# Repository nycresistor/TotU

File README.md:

TotU
====

Temple of the Unticketed

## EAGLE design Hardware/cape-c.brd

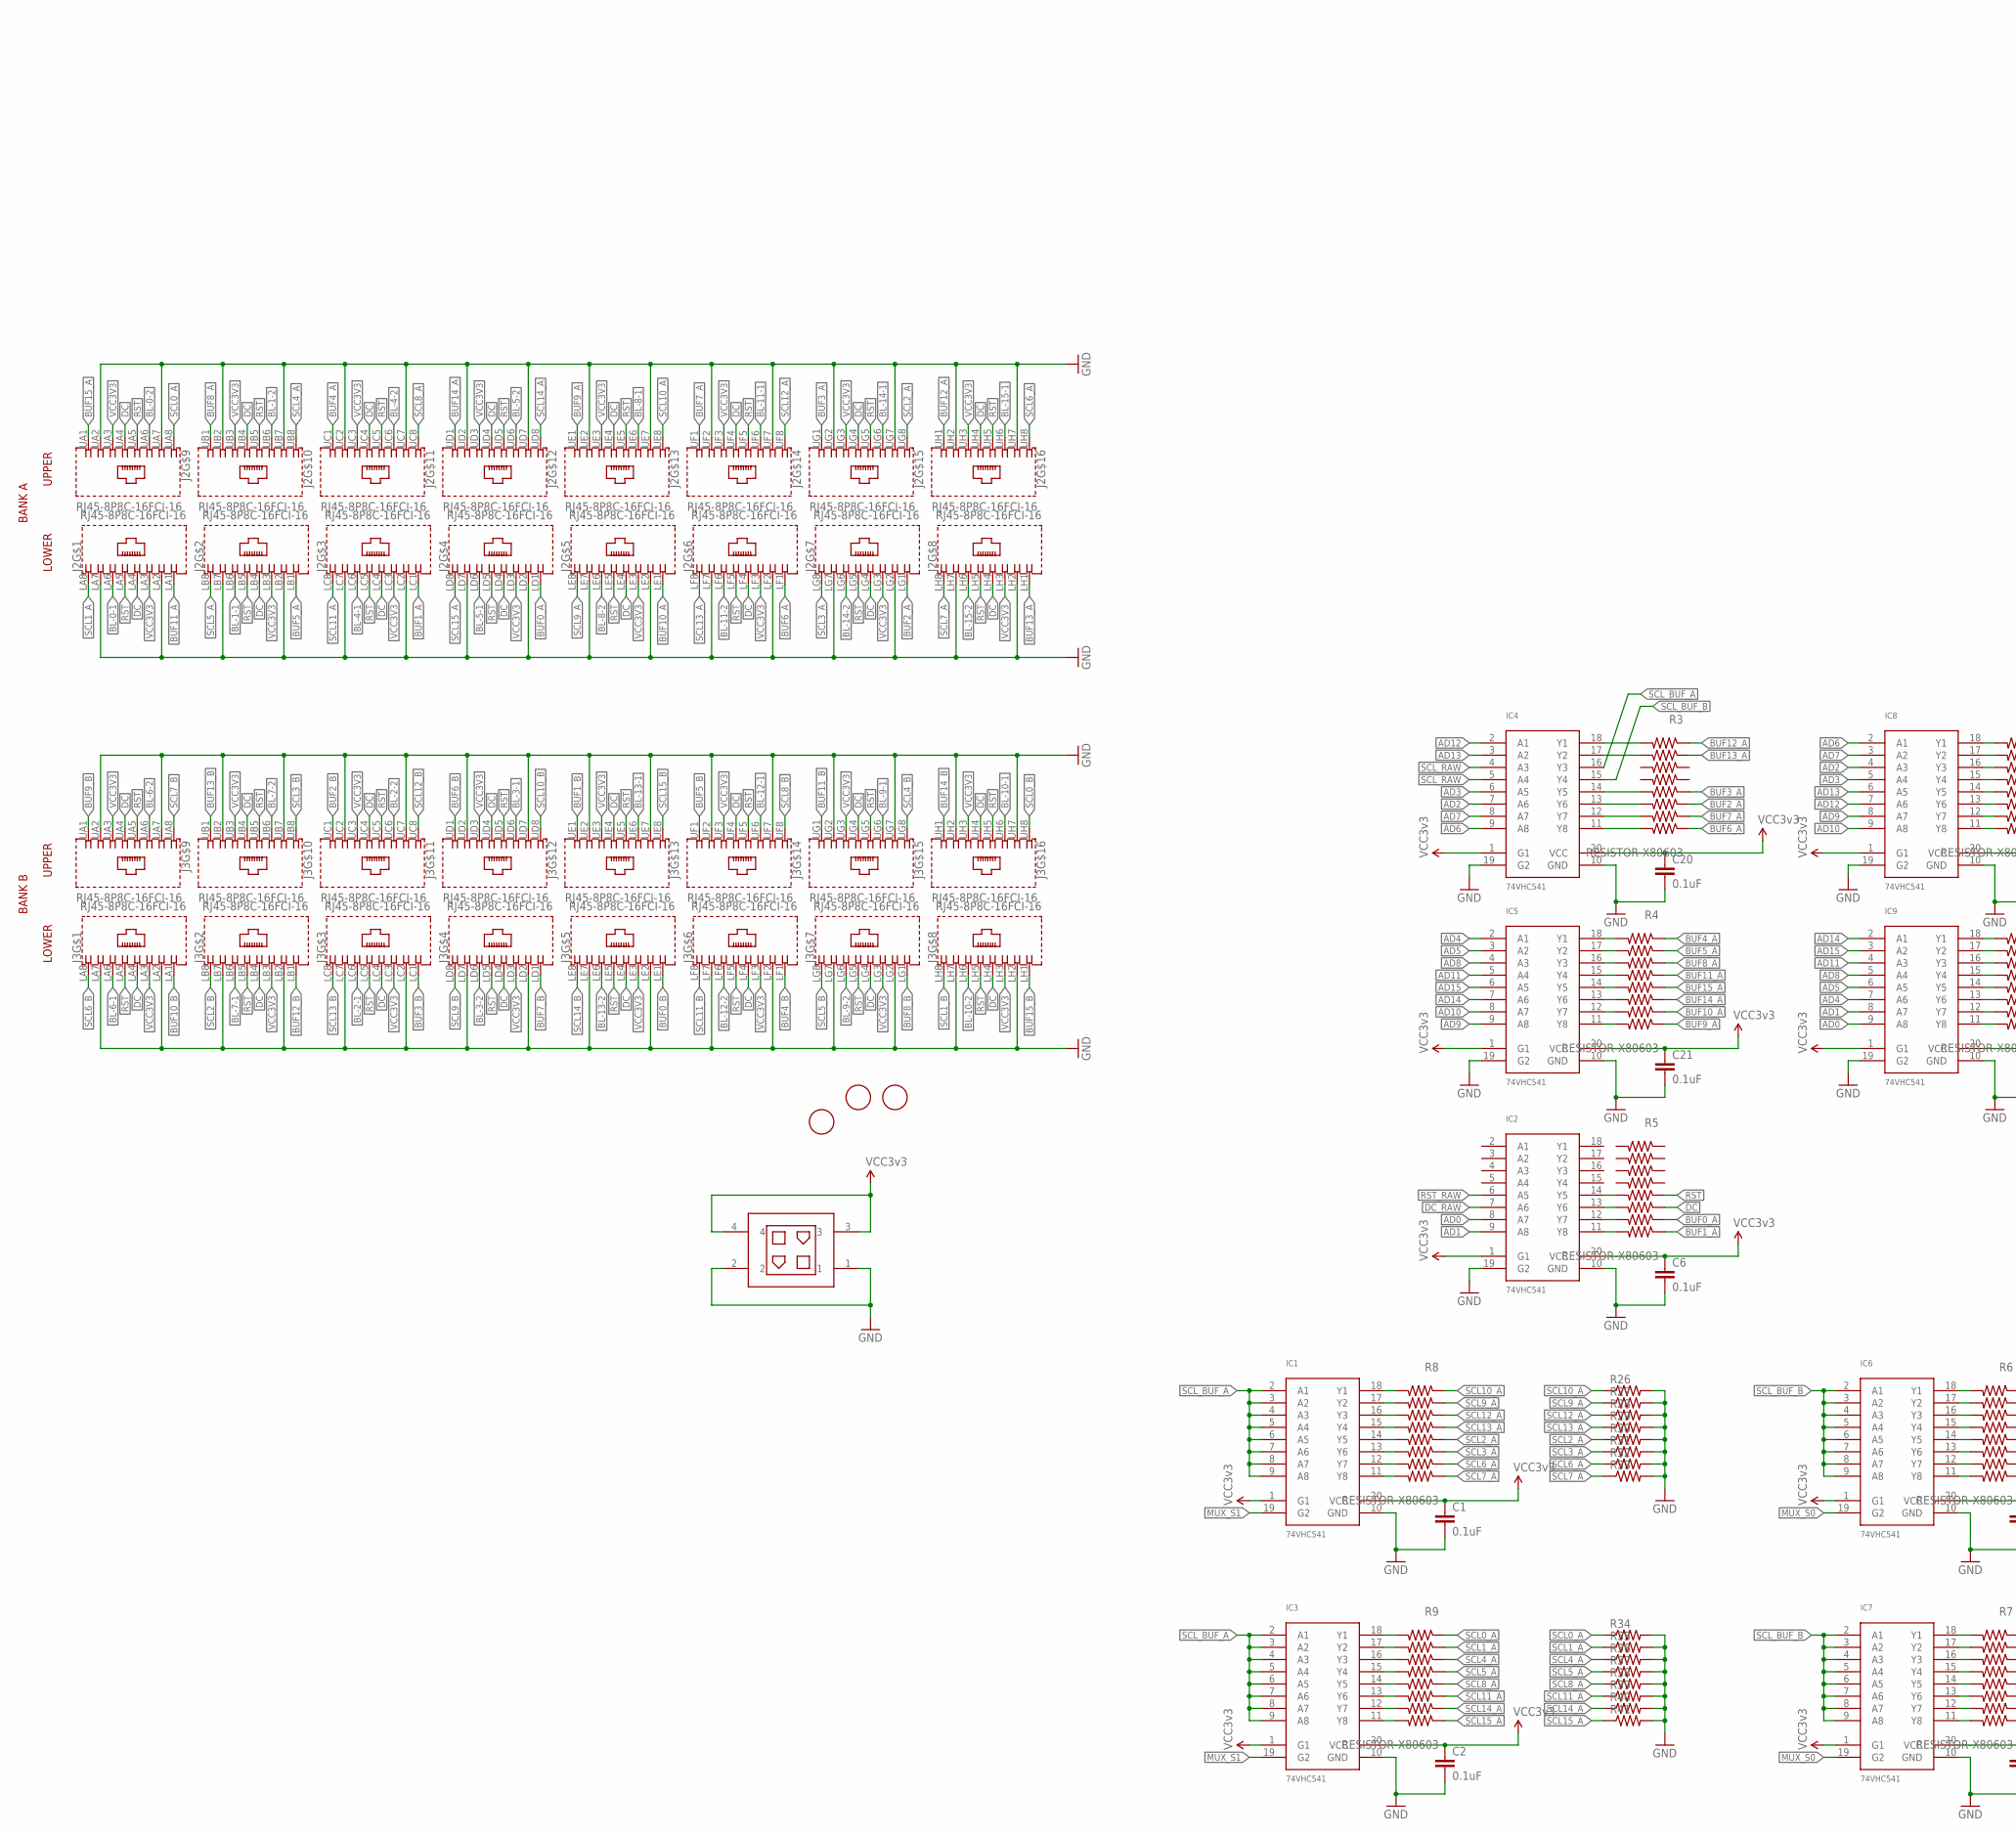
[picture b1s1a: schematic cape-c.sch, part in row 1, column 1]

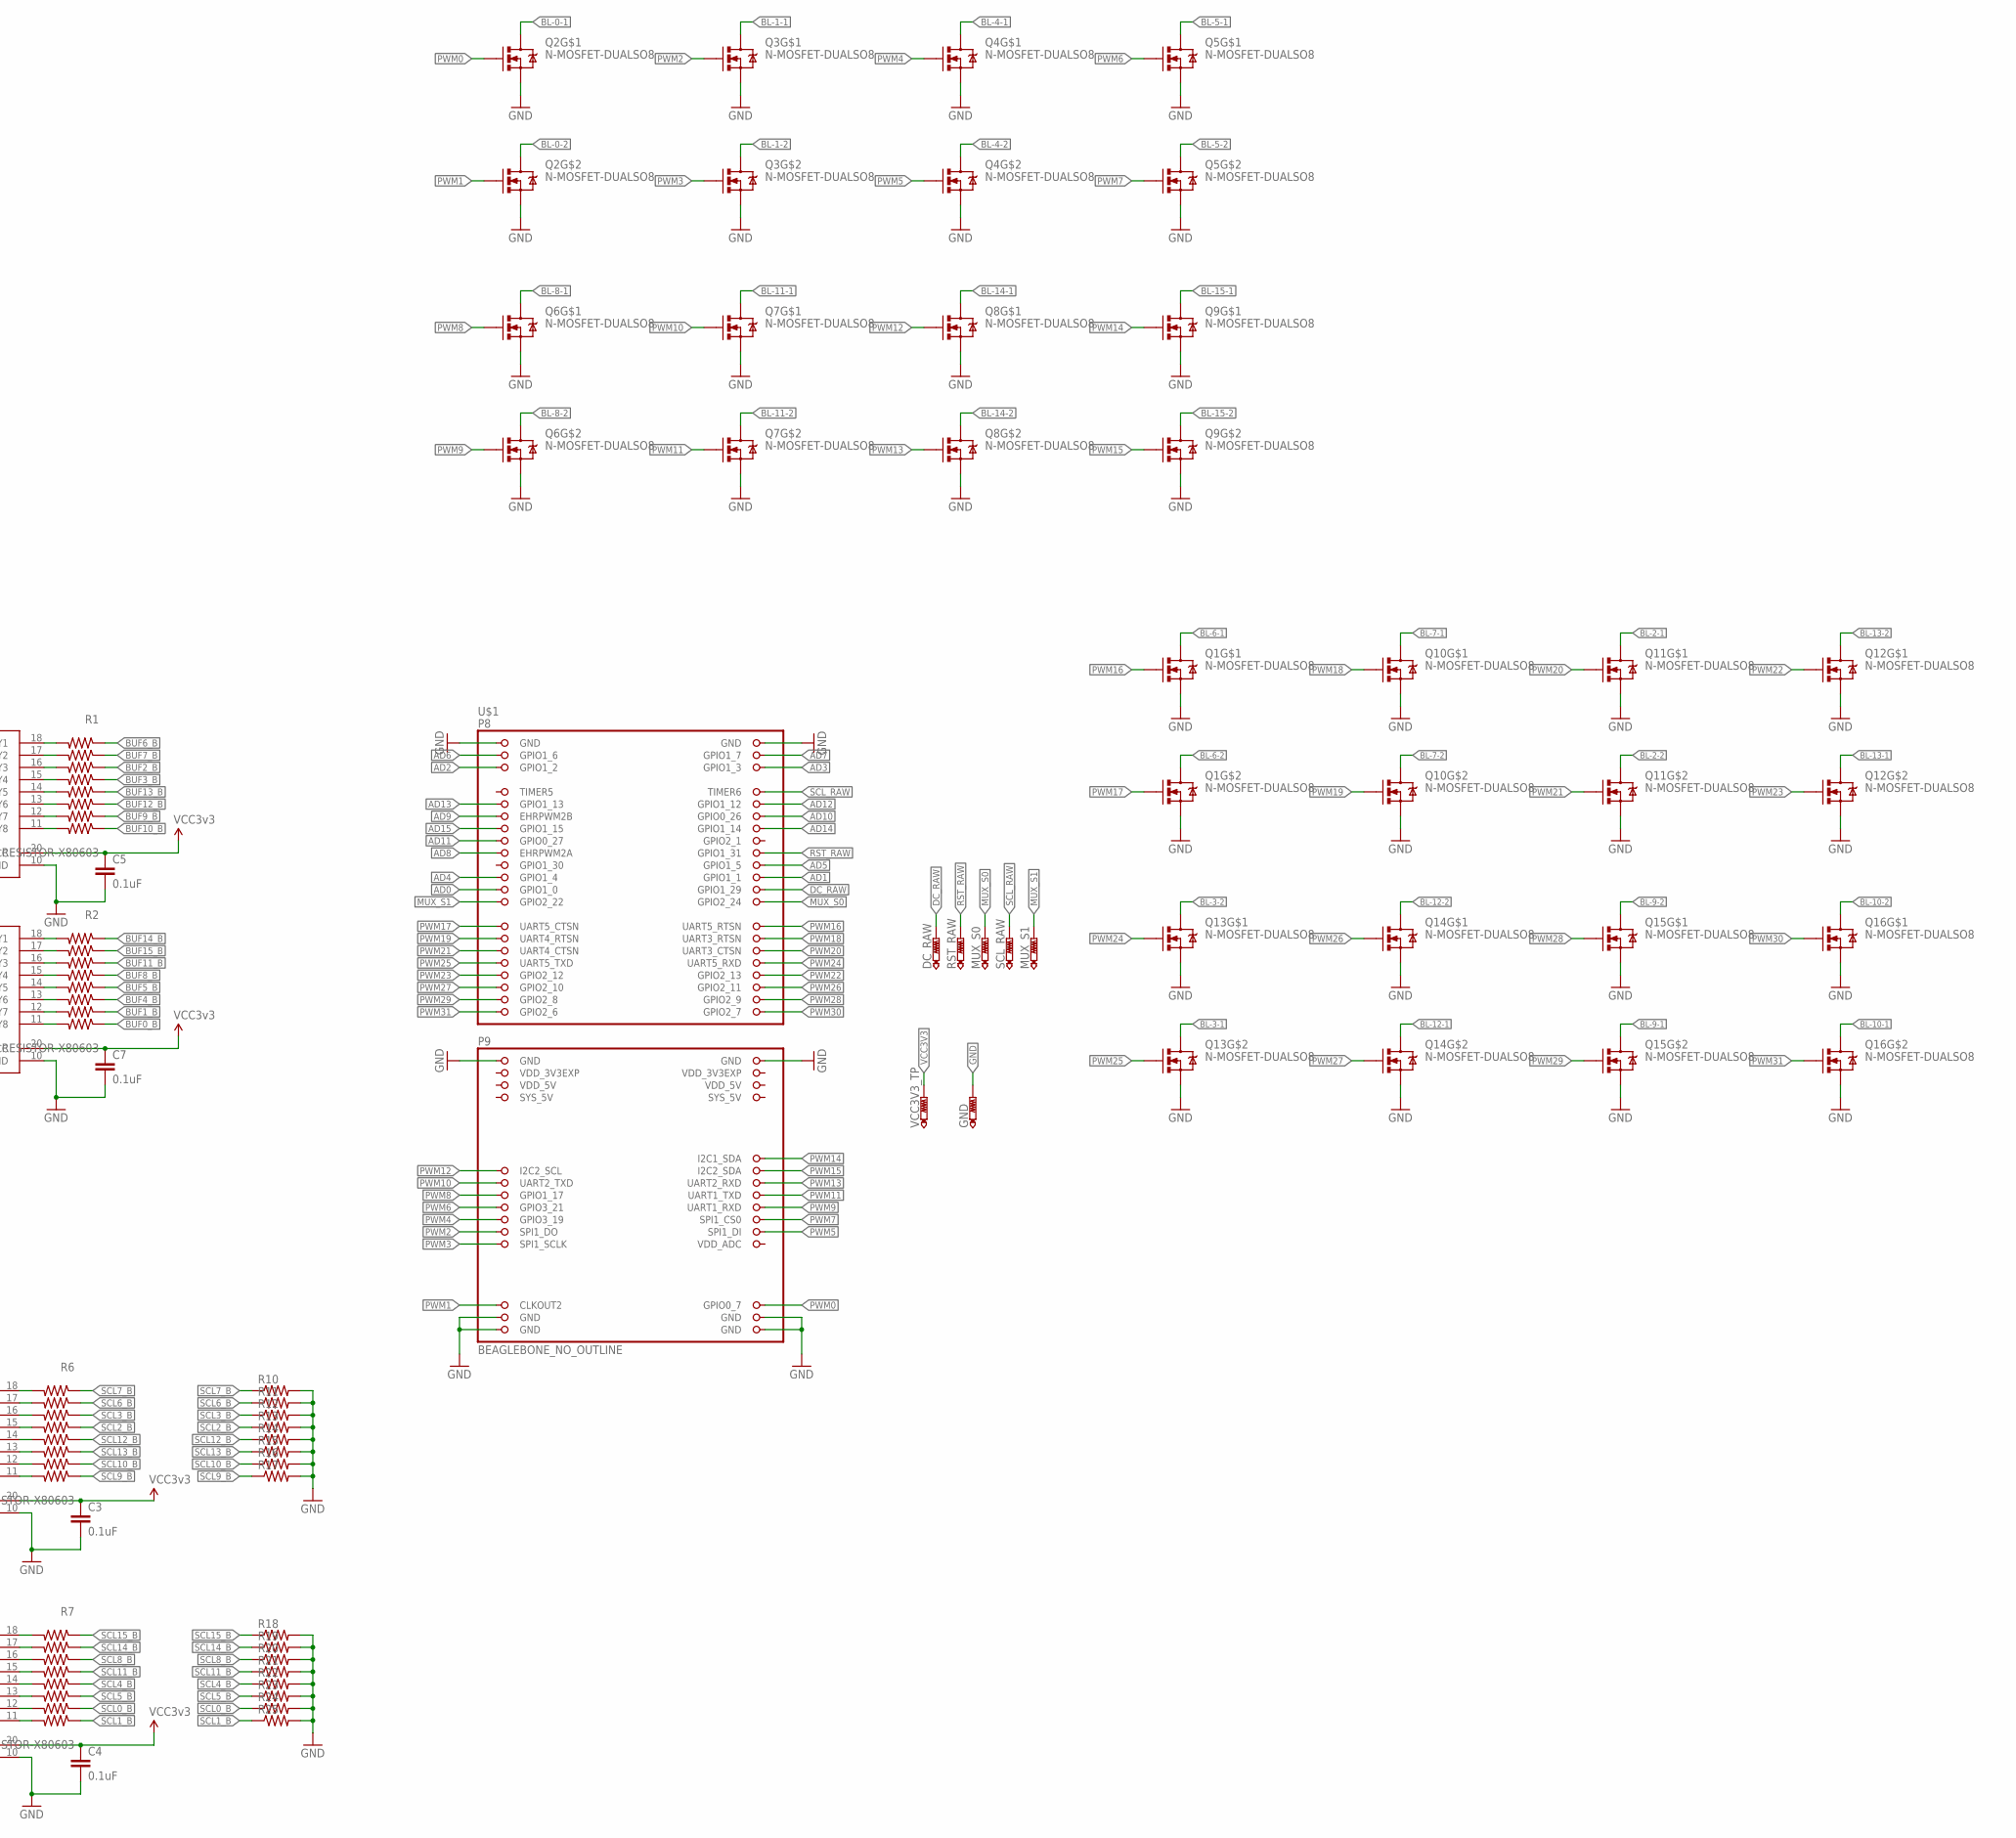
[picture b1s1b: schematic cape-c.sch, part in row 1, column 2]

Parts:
C1, C2, C3, C4, C5, C6, C7, C20, C21: 0.1uF; 0805
DC_RAW: PTR1TP10R; TP10R
GND: PTR1TP15SQ; TP15SQ
IC1, IC2, IC3, IC4, IC5, IC6, IC7, IC8, IC9: 74VHC541; TSSOP20; PARTNO MC74LCX245DTR2G
J1: MOLEX-P4
J2, J3: RJ45-8P8C-16FCI-16; FCI-10118074-500A010LF; PARTNO 10118074-500A010LF
MUX_S0, MUX_S1: PTR1TP10R; TP10R
Q1, Q2, Q3, Q4, Q5, Q6, Q7, Q8, Q9, Q10, Q11, Q12, Q13, Q14, Q15, Q16: N-MOSFET-DUALSO8; SO8; PARTNO DMN6040SSD-13
R1, R2, R3, R4, R5, R6, R7, R8, R9: RESISTOR-X80603; R0603-X8; PARTNO 742C163220JP
R10, R11, R12, R13, R14, R15, R16, R17, R18, R19, R20, R21, R22, R23, R24, R25, R26, R27, R28, R29, R30, R31, R32, R33, R34, R35, R36, R37, R38, R39, R40, R41: RESISTOR0603-RES; 0603-RES
RST_RAW: PTR1TP10R; TP10R
SCL_RAW: PTR1TP10R; TP10R
U$1: BEAGLEBONE_NO_OUTLINE; BEAGLEBONE_SHIELD_NO_OUTLINE
U$4, U$5, U$6: FIDUCIAL; FIDUCIAL_1MM
VCC3V3_TP: PTR1TP15R; TP15R

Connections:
AD0: IC2.8 (A7), IC9.9 (A8), U$1.25 (GPIO1_0)
AD1: IC2.9 (A8), IC9.8 (A7), U$1.24 (GPIO1_1)
AD2: IC4.7 (A6), IC8.4 (A3), U$1.5 (GPIO1_2)
AD3: IC4.6 (A5), IC8.5 (A4), U$1.6 (GPIO1_3)
AD4: IC5.2 (A1), IC9.7 (A6), U$1.23 (GPIO1_4)
AD5: IC5.3 (A2), IC9.6 (A5), U$1.22 (GPIO1_5)
AD6: IC4.9 (A8), IC8.2 (A1), U$1.3 (GPIO1_6)
AD7: IC4.8 (A7), IC8.3 (A2), U$1.4 (GPIO1_7)
AD8: IC5.4 (A3), IC9.5 (A4), U$1.19 (EHRPWM2A)
AD9: IC5.9 (A8), IC8.8 (A7), U$1.13 (EHRPWM2B)
AD10: IC5.8 (A7), IC8.9 (A8), U$1.14 (GPIO0_26)
AD11: IC5.5 (A4), IC9.4 (A3), U$1.17 (GPIO0_27)
AD12: IC4.2 (A1), IC8.7 (A6), U$1.12 (GPIO1_12)
AD13: IC4.3 (A2), IC8.6 (A5), U$1.11 (GPIO1_13)
AD14: IC5.7 (A6), IC9.2 (A1), U$1.16 (GPIO1_14)
AD15: IC5.6 (A5), IC9.3 (A2), U$1.15 (GPIO1_15)
BL-0-1: J2.LA6 (6), Q2.7 (D), Q2.8 (D)
BL-0-2: J2.UA6 (6), Q2.5 (D), Q2.6 (D)
BL-1-1: J2.LB6 (6), Q3.7 (D), Q3.8 (D)
BL-1-2: J2.UB6 (6), Q3.5 (D), Q3.6 (D)
BL-2-1: J3.LC6 (6), Q11.7 (D), Q11.8 (D)
BL-2-2: J3.UC6 (6), Q11.5 (D), Q11.6 (D)
BL-3-1: J3.UD6 (6), Q13.5 (D), Q13.6 (D)
BL-3-2: J3.LD6 (6), Q13.7 (D), Q13.8 (D)
BL-4-1: J2.LC6 (6), Q4.7 (D), Q4.8 (D)
BL-4-2: J2.UC6 (6), Q4.5 (D), Q4.6 (D)
BL-5-1: J2.LD6 (6), Q5.7 (D), Q5.8 (D)
BL-5-2: J2.UD6 (6), Q5.5 (D), Q5.6 (D)
BL-6-1: J3.LA6 (6), Q1.7 (D), Q1.8 (D)
BL-6-2: J3.UA6 (6), Q1.5 (D), Q1.6 (D)
BL-7-1: J3.LB6 (6), Q10.7 (D), Q10.8 (D)
BL-7-2: J3.UB6 (6), Q10.5 (D), Q10.6 (D)
BL-8-1: J2.UE6 (6), Q6.7 (D), Q6.8 (D)
BL-8-2: J2.LE6 (6), Q6.5 (D), Q6.6 (D)
BL-9-1: J3.UG6 (6), Q15.5 (D), Q15.6 (D)
BL-9-2: J3.LG6 (6), Q15.7 (D), Q15.8 (D)
BL-10-1: J3.UH6 (6), Q16.5 (D), Q16.6 (D)
BL-10-2: J3.LH6 (6), Q16.7 (D), Q16.8 (D)
BL-11-1: J2.UF6 (6), Q7.7 (D), Q7.8 (D)
BL-11-2: J2.LF6 (6), Q7.5 (D), Q7.6 (D)
BL-12-1: J3.UF6 (6), Q14.5 (D), Q14.6 (D)
BL-12-2: J3.LF6 (6), Q14.7 (D), Q14.8 (D)
BL-13-1: J3.UE6 (6), Q12.5 (D), Q12.6 (D)
BL-13-2: J3.LE6 (6), Q12.7 (D), Q12.8 (D)
BL-14-1: J2.UG6 (6), Q8.7 (D), Q8.8 (D)
BL-14-2: J2.LG6 (6), Q8.5 (D), Q8.6 (D)
BL-15-1: J2.UH6 (6), Q9.7 (D), Q9.8 (D)
BL-15-2: J2.LH6 (6), Q9.5 (D), Q9.6 (D)
BUF0_A: J2.LD1 (1), R5.7A (7B)
BUF0_B: J3.LE1 (1), R2.8A (8B)
BUF1_A: J2.LC1 (1), R5.8A (8B)
BUF1_B: J3.UE1 (1), R2.7A (7B)
BUF2_A: J2.LG1 (1), R3.6A (6B)
BUF2_B: J3.UC1 (1), R1.3A (3B)
BUF3_A: J2.UG1 (1), R3.5A (5B)
BUF3_B: J3.LC1 (1), R1.4A (4B)
BUF4_A: J2.UC1 (1), R4.1A (1B)
BUF4_B: J3.LF1 (1), R2.6A (6B)
BUF5_A: J2.LB1 (1), R4.2A (2B)
BUF5_B: J3.UF1 (1), R2.5A (5B)
BUF6_A: J2.LF1 (1), R3.8A (8B)
BUF6_B: J3.UD1 (1), R1.1A (1B)
BUF7_A: J2.UF1 (1), R3.7A (7B)
BUF7_B: J3.LD1 (1), R1.2A (2B)
BUF8_A: J2.UB1 (1), R4.3A (3B)
BUF8_B: J3.LG1 (1), R2.4A (4B)
BUF9_A: J2.UE1 (1), R4.8A (8B)
BUF9_B: J3.UA1 (1), R1.7A (7B)
BUF10_A: J2.LE1 (1), R4.7A (7B)
BUF10_B: J3.LA1 (1), R1.8A (8B)
BUF11_A: J2.LA1 (1), R4.4A (4B)
BUF11_B: J3.UG1 (1), R2.3A (3B)
BUF12_A: J2.UH1 (1), R3.1A (1B)
BUF12_B: J3.LB1 (1), R1.6A (6B)
BUF13_A: J2.LH1 (1), R3.2A (2B)
BUF13_B: J3.UB1 (1), R1.5A (5B)
BUF14_A: J2.UD1 (1), R4.6A (6B)
BUF14_B: J3.UH1 (1), R2.1A (1B)
BUF15_A: J2.UA1 (1), R4.5A (5B)
BUF15_B: J3.LH1 (1), R2.2A (2B)
DC: J2.LA4 (4), J2.LB4 (4), J2.LC4 (4), J2.LD4 (4), J2.LE4 (4), J2.LF4 (4), J2.LG4 (4), J2.LH4 (4), J2.UA4 (4), J2.UB4 (4), J2.UC4 (4), J2.UD4 (4), J2.UE4 (4), J2.UF4 (4), J2.UG4 (4), J2.UH4 (4), J3.LA4 (4), J3.LB4 (4), J3.LC4 (4), J3.LD4 (4), J3.LE4 (4), J3.LF4 (4), J3.LG4 (4), J3.LH4 (4), J3.UA4 (4), J3.UB4 (4), J3.UC4 (4), J3.UD4 (4), J3.UE4 (4), J3.UF4 (4), J3.UG4 (4), J3.UH4 (4), R5.6A (6B)
DC_RAW: DC_RAW.TP, IC2.7 (A6), U$1.26 (GPIO1_29)
GND: C1.2, C2.2, C3.2, C4.2, C5.2, C6.2, C7.2, C20.2, C21.2, GND.TP, IC1.10 (GND), IC2.10 (GND), IC2.19 (G2), IC3.10 (GND), IC4.10 (GND), IC4.19 (G2), IC5.10 (GND), IC5.19 (G2), IC6.10 (GND), IC7.10 (GND), IC8.10 (GND), IC8.19 (G2), IC9.10 (GND), IC9.19 (G2), J1.1, J1.2, J2.LA2 (2), J2.LA7 (7), J2.LB2 (2), J2.LB7 (7), J2.LC2 (2), J2.LC7 (7), J2.LD2 (2), J2.LD7 (7), J2.LE2 (2), J2.LE7 (7), J2.LF2 (2), J2.LF7 (7), J2.LG2 (2), J2.LG7 (7), J2.LH2 (2), J2.LH7 (7), J2.UA2 (2), J2.UA7 (7), J2.UB2 (2), J2.UB7 (7), J2.UC2 (2), J2.UC7 (7), J2.UD2 (2), J2.UD7 (7), J2.UE2 (2), J2.UE7 (7), J2.UF2 (2), J2.UF7 (7), J2.UG2 (2), J2.UG7 (7), J2.UH2 (2), J2.UH7 (7), J3.LA2 (2), J3.LA7 (7), J3.LB2 (2), J3.LB7 (7), J3.LC2 (2), J3.LC7 (7), J3.LD2 (2), J3.LD7 (7), J3.LE2 (2), J3.LE7 (7), J3.LF2 (2), J3.LF7 (7), J3.LG2 (2), J3.LG7 (7), J3.LH2 (2), J3.LH7 (7), J3.UA2 (2), J3.UA7 (7), J3.UB2 (2), J3.UB7 (7), J3.UC2 (2), J3.UC7 (7), J3.UD2 (2), J3.UD7 (7), J3.UE2 (2), J3.UE7 (7), J3.UF2 (2), J3.UF7 (7), J3.UG2 (2), J3.UG7 (7), J3.UH2 (2), J3.UH7 (7), Q1.1 (S), Q1.3 (S), Q2.1 (S), Q2.3 (S), Q3.1 (S), Q3.3 (S), Q4.1 (S), Q4.3 (S), Q5.1 (S), Q5.3 (S), Q6.1 (S), Q6.3 (S), Q7.1 (S), Q7.3 (S), Q8.1 (S), Q8.3 (S), Q9.1 (S), Q9.3 (S), Q10.1 (S), Q10.3 (S), Q11.1 (S), Q11.3 (S), Q12.1 (S), Q12.3 (S), Q13.1 (S), Q13.3 (S), Q14.1 (S), Q14.3 (S), Q15.1 (S), Q15.3 (S), Q16.1 (S), Q16.3 (S), R10.2, R11.2, R12.2, R13.2, R14.2, R15.2, R16.2, R17.2, R18.2, R19.2, R20.2, R21.2, R22.2, R23.2, R24.2, R25.2, R26.2, R27.2, R28.2, R29.2, R30.2, R31.2, R32.2, R33.2, R34.2, R35.2, R36.2, R37.2, R38.2, R39.2, R40.2, R41.2, U$1.1 (GND), U$1.2 (GND), U$1.47 (GND), U$1.48 (GND), U$1.89 (GND), U$1.90 (GND), U$1.91 (GND), U$1.92 (GND)
MUX_S0: IC6.19 (G2), IC7.19 (G2), MUX_S0.TP, U$1.28 (GPIO2_24)
MUX_S1: IC1.19 (G2), IC3.19 (G2), MUX_S1.TP, U$1.27 (GPIO2_22)
unnamed: IC2.14 (Y5), R5.5B (5A)
unnamed: IC2.13 (Y6), R5.6B (6A)
unnamed: IC8.18 (Y1), R1.1B (1A)
unnamed: IC8.17 (Y2), R1.2B (2A)
unnamed: IC8.16 (Y3), R1.3B (3A)
unnamed: IC8.15 (Y4), R1.4B (4A)
unnamed: IC8.14 (Y5), R1.5B (5A)
unnamed: IC8.13 (Y6), R1.6B (6A)
unnamed: IC8.12 (Y7), R1.7B (7A)
unnamed: IC8.11 (Y8), R1.8B (8A)
unnamed: IC9.18 (Y1), R2.1B (1A)
unnamed: IC9.17 (Y2), R2.2B (2A)
unnamed: IC9.16 (Y3), R2.3B (3A)
unnamed: IC9.15 (Y4), R2.4B (4A)
unnamed: IC9.14 (Y5), R2.5B (5A)
unnamed: IC9.13 (Y6), R2.6B (6A)
unnamed: IC9.12 (Y7), R2.7B (7A)
unnamed: IC9.11 (Y8), R2.8B (8A)
unnamed: IC5.18 (Y1), R4.1B (1A)
unnamed: IC5.17 (Y2), R4.2B (2A)
unnamed: IC5.16 (Y3), R4.3B (3A)
unnamed: IC5.15 (Y4), R4.4B (4A)
unnamed: IC5.13 (Y6), R4.6B (6A)
unnamed: IC5.14 (Y5), R4.5B (5A)
unnamed: IC5.12 (Y7), R4.7B (7A)
unnamed: IC5.11 (Y8), R4.8B (8A)
unnamed: IC4.18 (Y1), R3.1B (1A)
unnamed: IC4.17 (Y2), R3.2B (2A)
unnamed: IC6.18 (Y1), R6.1B (1A)
unnamed: IC2.12 (Y7), R5.7B (7A)
unnamed: IC4.14 (Y5), R3.5B (5A)
unnamed: IC4.13 (Y6), R3.6B (6A)
unnamed: IC4.12 (Y7), R3.7B (7A)
unnamed: IC4.11 (Y8), R3.8B (8A)
unnamed: IC2.11 (Y8), R5.8B (8A)
unnamed: IC6.17 (Y2), R6.2B (2A)
unnamed: IC6.16 (Y3), R6.3B (3A)
unnamed: IC6.15 (Y4), R6.4B (4A)
unnamed: IC6.14 (Y5), R6.5B (5A)
unnamed: IC6.13 (Y6), R6.6B (6A)
unnamed: IC6.12 (Y7), R6.7B (7A)
unnamed: IC6.11 (Y8), R6.8B (8A)
unnamed: IC7.18 (Y1), R7.1B (1A)
unnamed: IC7.17 (Y2), R7.2B (2A)
unnamed: IC7.15 (Y4), R7.4B (4A)
unnamed: IC7.16 (Y3), R7.3B (3A)
unnamed: IC7.14 (Y5), R7.5B (5A)
unnamed: IC7.12 (Y7), R7.7B (7A)
unnamed: IC7.13 (Y6), R7.6B (6A)
unnamed: IC7.11 (Y8), R7.8B (8A)
unnamed: IC1.18 (Y1), R8.1B (1A)
unnamed: IC1.17 (Y2), R8.2B (2A)
unnamed: IC1.16 (Y3), R8.3B (3A)
unnamed: IC1.15 (Y4), R8.4B (4A)
unnamed: IC1.14 (Y5), R8.5B (5A)
unnamed: IC1.13 (Y6), R8.6B (6A)
unnamed: IC1.12 (Y7), R8.7B (7A)
unnamed: IC1.11 (Y8), R8.8B (8A)
unnamed: IC3.18 (Y1), R9.1B (1A)
unnamed: IC3.17 (Y2), R9.2B (2A)
unnamed: IC3.16 (Y3), R9.3B (3A)
unnamed: IC3.15 (Y4), R9.4B (4A)
unnamed: IC3.14 (Y5), R9.5B (5A)
unnamed: IC3.13 (Y6), R9.6B (6A)
unnamed: IC3.12 (Y7), R9.7B (7A)
unnamed: IC3.11 (Y8), R9.8B (8A)
PWM0: Q2.2 (G), U$1.88 (GPIO0_7)
PWM1: Q2.4 (G), U$1.87 (CLKOUT2)
PWM2: Q3.2 (G), U$1.75 (SPI1_DO)
PWM3: Q3.4 (G), U$1.77 (SPI1_SCLK)
PWM4: Q4.2 (G), U$1.73 (GPIO3_19)
PWM5: Q4.4 (G), U$1.76 (SPI1_DI)
PWM6: Q5.2 (G), U$1.71 (GPIO3_21)
PWM7: Q5.4 (G), U$1.74 (SPI1_CS0)
PWM8: Q6.2 (G), U$1.69 (GPIO1_17)
PWM9: Q6.4 (G), U$1.72 (UART1_RXD)
PWM10: Q7.2 (G), U$1.67 (UART2_TXD)
PWM11: Q7.4 (G), U$1.70 (UART1_TXD)
PWM12: Q8.2 (G), U$1.65 (I2C2_SCL)
PWM13: Q8.4 (G), U$1.68 (UART2_RXD)
PWM14: Q9.2 (G), U$1.64 (I2C1_SDA)
PWM15: Q9.4 (G), U$1.66 (I2C2_SDA)
PWM16: Q1.2 (G), U$1.32 (UART5_RTSN)
PWM17: Q1.4 (G), U$1.31 (UART5_CTSN)
PWM18: Q10.2 (G), U$1.34 (UART3_RTSN)
PWM19: Q10.4 (G), U$1.33 (UART4_RTSN)
PWM20: Q11.2 (G), U$1.36 (UART3_CTSN)
PWM21: Q11.4 (G), U$1.35 (UART4_CTSN)
PWM22: Q12.2 (G), U$1.40 (GPIO2_13)
PWM23: Q12.4 (G), U$1.39 (GPIO2_12)
PWM24: Q13.2 (G), U$1.38 (UART5_RXD)
PWM25: Q13.4 (G), U$1.37 (UART5_TXD)
PWM26: Q14.2 (G), U$1.42 (GPIO2_11)
PWM27: Q14.4 (G), U$1.41 (GPIO2_10)
PWM28: Q15.2 (G), U$1.44 (GPIO2_9)
PWM29: Q15.4 (G), U$1.43 (GPIO2_8)
PWM30: Q16.2 (G), U$1.46 (GPIO2_7)
PWM31: Q16.4 (G), U$1.45 (GPIO2_6)
RST: J2.LA5 (5), J2.LB5 (5), J2.LC5 (5), J2.LD5 (5), J2.LE5 (5), J2.LF5 (5), J2.LG5 (5), J2.LH5 (5), J2.UA5 (5), J2.UB5 (5), J2.UC5 (5), J2.UD5 (5), J2.UE5 (5), J2.UF5 (5), J2.UG5 (5), J2.UH5 (5), J3.LA5 (5), J3.LB5 (5), J3.LC5 (5), J3.LD5 (5), J3.LE5 (5), J3.LF5 (5), J3.LG5 (5), J3.LH5 (5), J3.UA5 (5), J3.UB5 (5), J3.UC5 (5), J3.UD5 (5), J3.UE5 (5), J3.UF5 (5), J3.UG5 (5), J3.UH5 (5), R5.5A (5B)
RST_RAW: IC2.6 (A5), RST_RAW.TP, U$1.20 (GPIO1_31)
SCL0_A: J2.UA8 (8), R9.1A (1B), R34.1
SCL0_B: J3.UH8 (8), R7.7A (7B), R24.1
SCL1_A: J2.LA8 (8), R9.2A (2B), R35.1
SCL1_B: J3.LH8 (8), R7.8A (8B), R25.1
SCL2_A: J2.UG8 (8), R8.5A (5B), R30.1
SCL2_B: J3.LB8 (8), R6.4A (4B), R13.1
SCL3_A: J2.LG8 (8), R8.6A (6B), R31.1
SCL3_B: J3.UB8 (8), R6.3A (3B), R12.1
SCL4_A: J2.UB8 (8), R9.3A (3B), R36.1
SCL4_B: J3.UG8 (8), R7.5A (5B), R22.1
SCL5_A: J2.LB8 (8), R9.4A (4B), R37.1
SCL5_B: J3.LG8 (8), R7.6A (6B), R23.1
SCL6_A: J2.UH8 (8), R8.7A (7B), R32.1
SCL6_B: J3.LA8 (8), R6.2A (2B), R11.1
SCL7_A: J2.LH8 (8), R8.8A (8B), R33.1
SCL7_B: J3.UA8 (8), R6.1A (1B), R10.1
SCL8_A: J2.UC8 (8), R9.5A (5B), R38.1
SCL8_B: J3.UF8 (8), R7.3A (3B), R20.1
SCL9_A: J2.LE8 (8), R8.2A (2B), R27.1
SCL9_B: J3.LD8 (8), R6.8A (8B), R17.1
SCL10_A: J2.UE8 (8), R8.1A (1B), R26.1
SCL10_B: J3.UD8 (8), R6.7A (7B), R16.1
SCL11_A: J2.LC8 (8), R9.6A (6B), R39.1
SCL11_B: J3.LF8 (8), R7.4A (4B), R21.1
SCL12_A: J2.UF8 (8), R8.3A (3B), R28.1
SCL12_B: J3.UC8 (8), R6.5A (5B), R14.1
SCL13_A: J2.LF8 (8), R8.4A (4B), R29.1
SCL13_B: J3.LC8 (8), R6.6A (6B), R15.1
SCL14_A: J2.UD8 (8), R9.7A (7B), R40.1
SCL14_B: J3.LE8 (8), R7.2A (2B), R19.1
SCL15_A: J2.LD8 (8), R9.8A (8B), R41.1
SCL15_B: J3.UE8 (8), R7.1A (1B), R18.1
SCL_BUF_A: IC1.2 (A1), IC1.3 (A2), IC1.4 (A3), IC1.5 (A4), IC1.6 (A5), IC1.7 (A6), IC1.8 (A7), IC1.9 (A8), IC3.2 (A1), IC3.3 (A2), IC3.4 (A3), IC3.5 (A4), IC3.6 (A5), IC3.7 (A6), IC3.8 (A7), IC3.9 (A8), IC4.16 (Y3)
SCL_BUF_B: IC4.15 (Y4), IC6.2 (A1), IC6.3 (A2), IC6.4 (A3), IC6.5 (A4), IC6.6 (A5), IC6.7 (A6), IC6.8 (A7), IC6.9 (A8), IC7.2 (A1), IC7.3 (A2), IC7.4 (A3), IC7.5 (A4), IC7.6 (A5), IC7.7 (A6), IC7.8 (A7), IC7.9 (A8)
SCL_RAW: IC4.4 (A3), IC4.5 (A4), SCL_RAW.TP, U$1.10 (TIMER6)
SYS_5V: U$1.53 (SYS_5V)
VCC3V3: C1.1, C2.1, C3.1, C4.1, C5.1, C6.1, C7.1, C20.1, C21.1, IC1.1 (G1), IC1.20 (VCC), IC2.1 (G1), IC2.20 (VCC), IC3.1 (G1), IC3.20 (VCC), IC4.1 (G1), IC4.20 (VCC), IC5.1 (G1), IC5.20 (VCC), IC6.1 (G1), IC6.20 (VCC), IC7.1 (G1), IC7.20 (VCC), IC8.1 (G1), IC8.20 (VCC), IC9.1 (G1), IC9.20 (VCC), J1.3, J1.4, J2.LA3 (3), J2.LB3 (3), J2.LC3 (3), J2.LD3 (3), J2.LE3 (3), J2.LF3 (3), J2.LG3 (3), J2.LH3 (3), J2.UA3 (3), J2.UB3 (3), J2.UC3 (3), J2.UD3 (3), J2.UE3 (3), J2.UF3 (3), J2.UG3 (3), J2.UH3 (3), J3.LA3 (3), J3.LB3 (3), J3.LC3 (3), J3.LD3 (3), J3.LE3 (3), J3.LF3 (3), J3.LG3 (3), J3.LH3 (3), J3.UA3 (3), J3.UB3 (3), J3.UC3 (3), J3.UD3 (3), J3.UE3 (3), J3.UF3 (3), J3.UG3 (3), J3.UH3 (3), VCC3V3_TP.TP
VDD_3V3EXP: U$1.49 (VDD_3V3EXP), U$1.50 (VDD_3V3EXP)
VDD_5V: U$1.51 (VDD_5V), U$1.52 (VDD_5V)

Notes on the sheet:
LOWER
UPPER
BANK B
BANK A

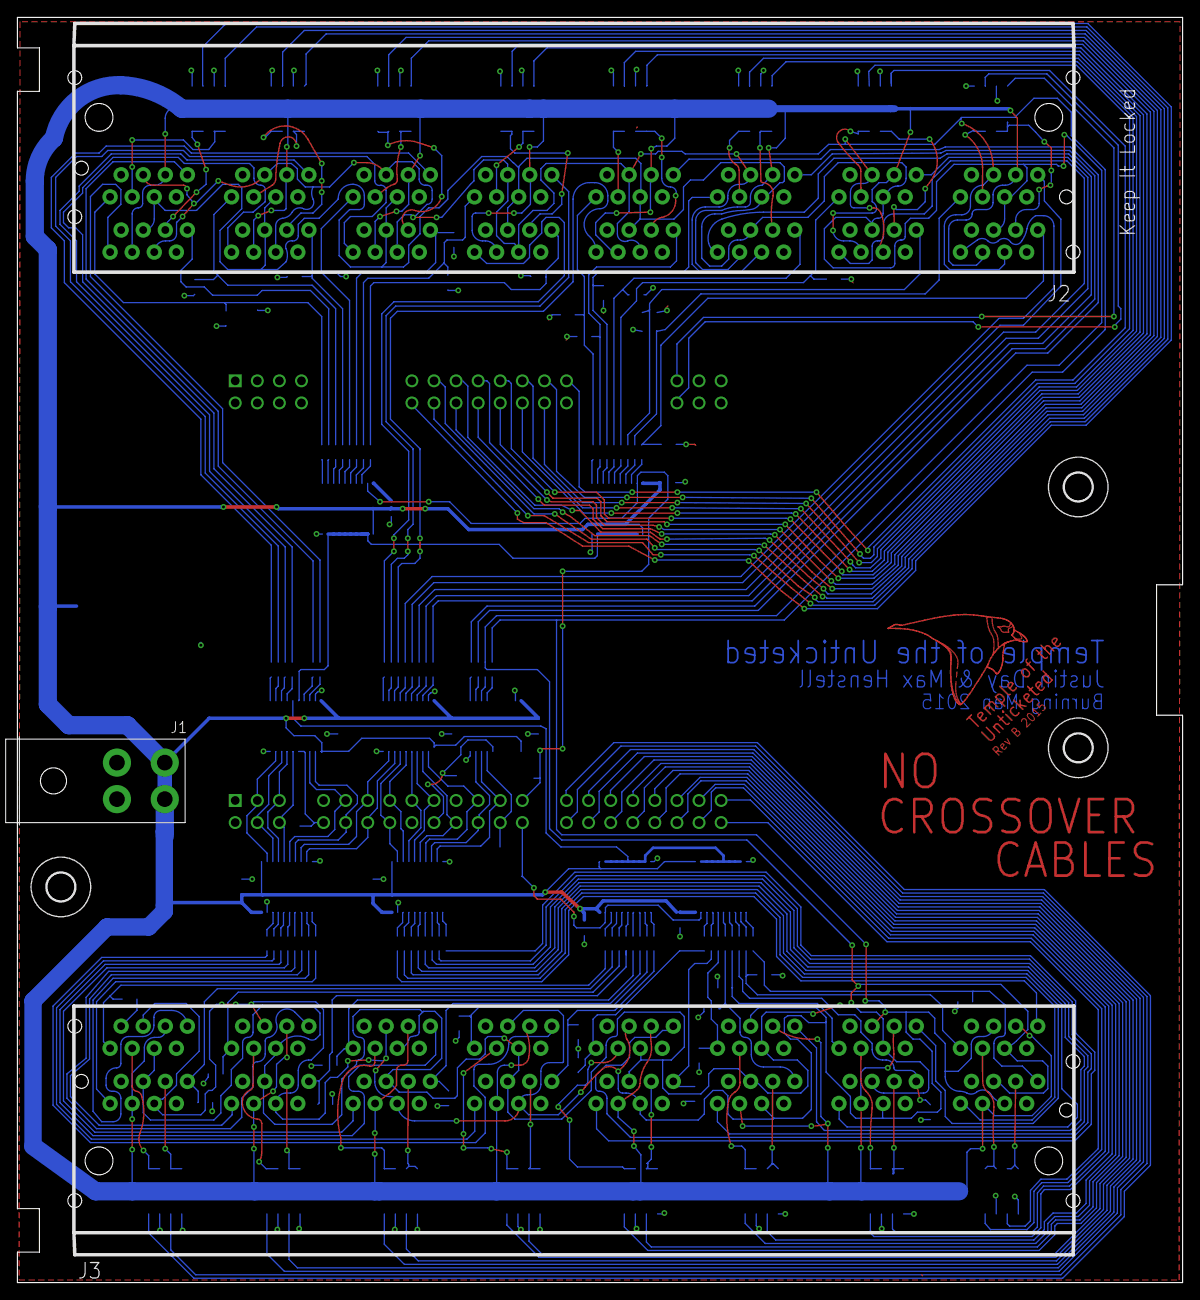
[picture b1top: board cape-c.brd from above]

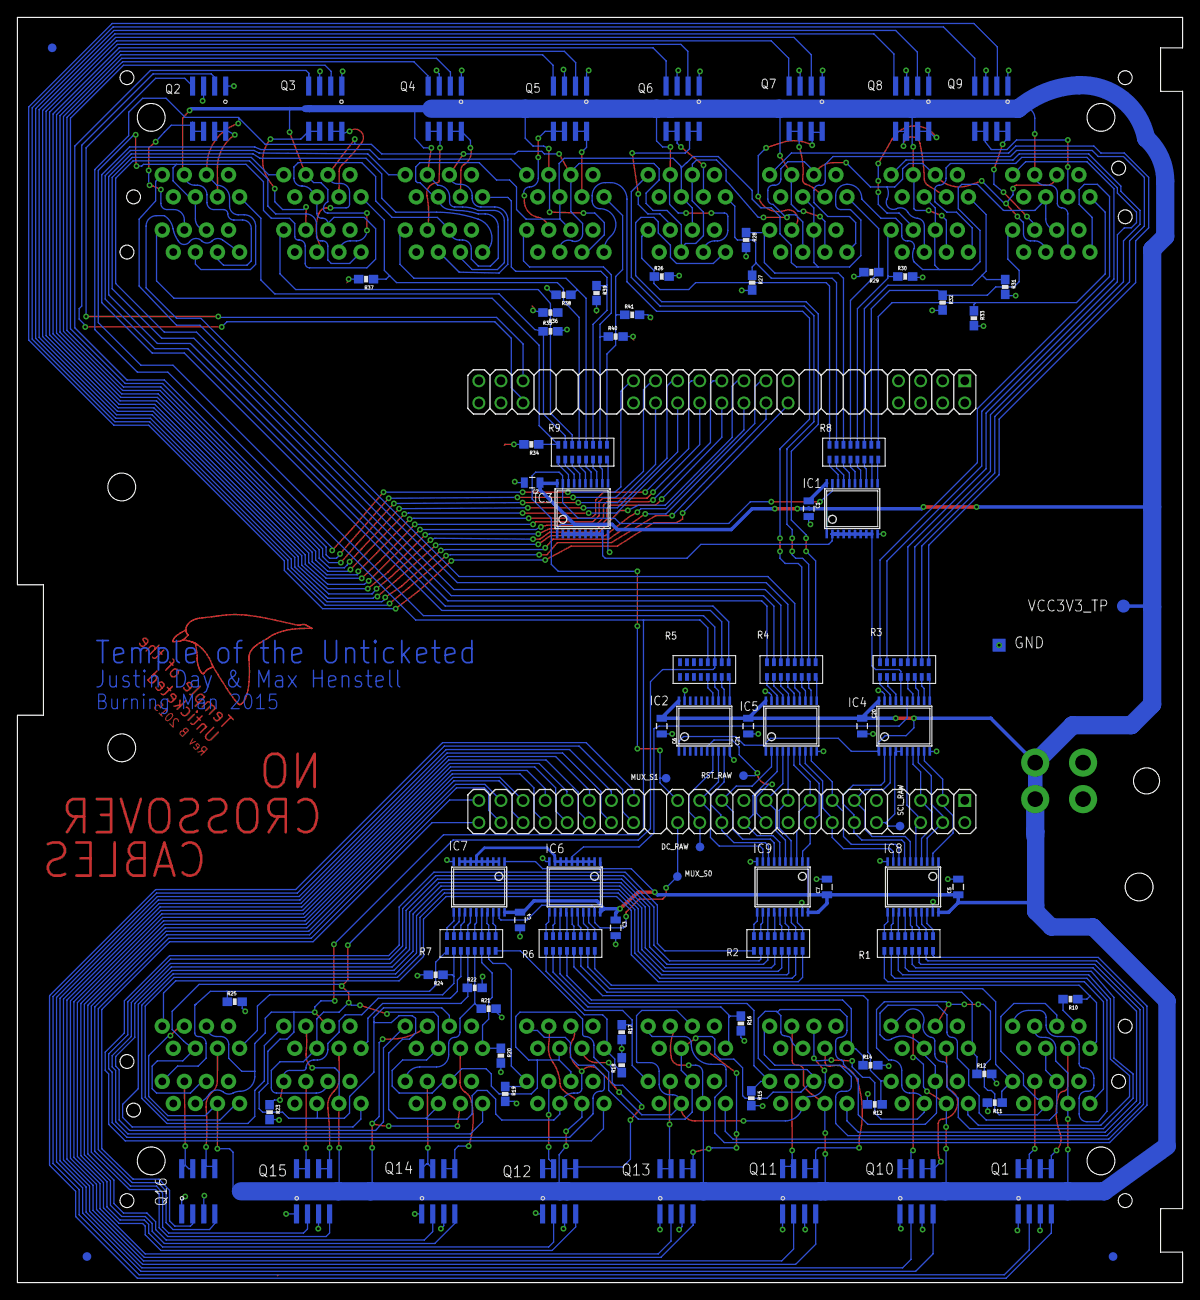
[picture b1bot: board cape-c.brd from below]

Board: 2 copper layers, 134.0 x 145.5 mm, 92 parts (86 on the bottom side), 223 nets.

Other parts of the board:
U$2, U$3, U$12: 3,2

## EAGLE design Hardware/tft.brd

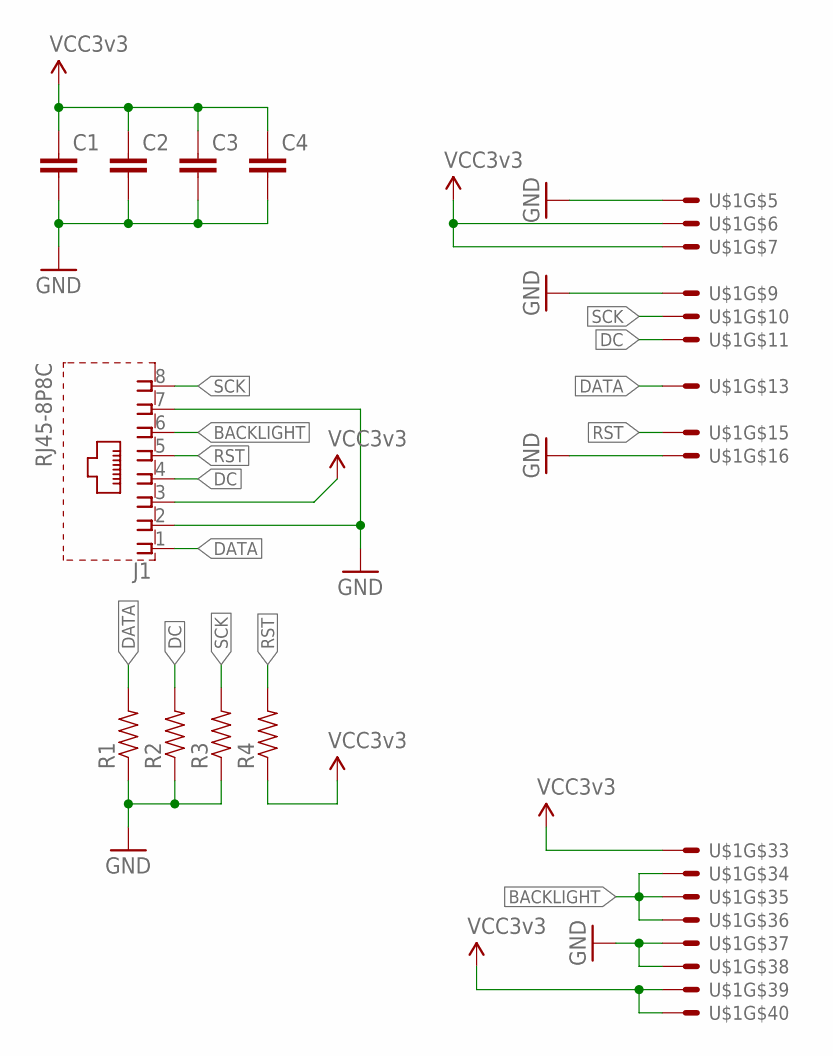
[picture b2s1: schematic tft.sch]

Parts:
C1, C2, C3, C4: CAP1206; 1206
J1: RJ45-8P8C; 54602-908LF; PARTNO 54602-908LF
R1, R2, R3, R4: RESISTOR0603; 0603-RES
U$1: XF2M-4015-WONKY

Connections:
BACKLIGHT: J1.6, U$1.34, U$1.35, U$1.36
DATA: J1.1, R1.2, U$1.13
DC: J1.4, R2.2, U$1.11
GND: C1.2, C2.2, C3.2, C4.2, J1.2, J1.7, R1.1, R2.1, R3.1, U$1.5, U$1.9, U$1.16, U$1.37, U$1.38
RST: J1.5, R4.2, U$1.15
SCK: J1.8, R3.2, U$1.10
VCC3V3: C1.1, C2.1, C3.1, C4.1, J1.3, R4.1, U$1.6, U$1.7, U$1.33, U$1.39, U$1.40

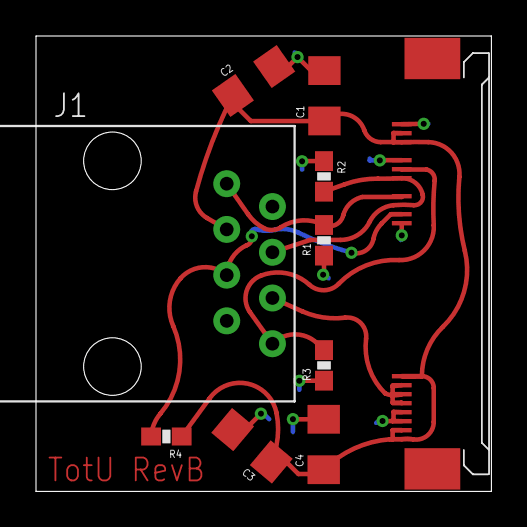
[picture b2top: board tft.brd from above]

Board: 2 copper layers, 25.3 x 25.3 mm, 10 parts (0 on the bottom side), 7 nets.

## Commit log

2014-09-16 init
2014-09-16 added legs
2014-09-16 moved screens outward slightly
2014-09-16 added supports
2014-09-17 adding new layout
2014-09-17 Housekeeping. Processing demo.
2014-09-17 adding cname
2014-09-17 made totems 3D, added legs
2014-09-17 housekeeping
2014-09-17 moving processing sketch into a like-named folder
2014-09-17 adding libraries
2014-09-17 removing old Totu.scad
2014-09-17 adding image
2014-09-17 adding pic to readme
2014-09-18 added person to scale, changed radius, cleanup and comments
2014-09-19 adding LCD frame
2014-09-19 TotU2 includes frame scad
2014-09-21 mostly working frame
2014-09-22 added frame lens
2014-09-22 cape init
2014-09-23 fixed crashing issue
2014-09-23 agency theme
2014-09-23 centering the viewable window
2014-09-23 added circuits to control backlights, but I'm going to pull them out for this revision
2014-09-23 removed led drivers, added backlight resistors
2014-09-23 adding draft pin map
2014-09-24 tweaking dimensions
2014-09-24 routing and pinmapping
2014-09-25 removing _site
2014-09-25 updating front page, team images, gitignore
2014-09-26 adding notes
2014-09-26 added pru pins to pinmap
2014-09-26 more pinmap info
2014-09-30 Futzing with textures
2014-09-30 adding pario2
2014-10-01 addig gitignore, updated test.c
2014-10-01 mapping L3 memory manually seems to be working between arm and pru
2014-10-04 Revised top image, about
2014-10-04 demo page
2014-10-04 adding gpmc to spi test
2014-10-05 updating gpmcTest
2014-10-05 now with 100% less compiler errors
2014-10-05 sucessfully sending setup commands for one screen
2014-10-06 works with individual bytes but not chunks
2014-10-06 single screen working at ~2fps
2014-10-06 horizontal, slightly faster?
2014-10-07 adding benchmarking code
2014-10-07 adding datasheets
2014-10-07 comments
2014-10-07 got rid of copy on writing, adding debugging functions
2014-10-07 DTS tweaking, build script
2014-10-14 Mapping camera video to cube
2014-11-19 Basic photo booth functionality working
2014-11-22 Refactored, added save, added flash
2014-11-25 Added drawings
2014-11-26 Updated to match pending LOI. Cleaned a lot up.
2014-11-26 Added contact, fixed title
2014-12-07 Working animations using GPMC
2014-12-08 adding imageConverter
2014-12-08 support multiple images maybe
2014-12-09 Working imageCoverter for up to 16 images
2014-12-10 Refactored to use less memory
2014-12-10 Broken using 16 images + numpy, benchmark 65 seconds
2014-12-10 Down to 25.7 secs per frame
2014-12-10 faster
2014-12-12 Working properly, using python rotation
2014-12-13 Updated cape schematic and library, added datasheets
2014-12-15 Working on board routing
2014-12-16 Routing
2014-12-17 Finished v1 board
2014-12-17 added bird and fixed dimensions
2014-12-18 adding tft pcb
2014-12-21 Automatic sequence discovery, cleanup
2014-12-21 Fixed dtbo makefile
2014-12-21 Fixing variable name, cleanup
2014-12-21 Adding modified pario that handles PWM
2014-12-21 Bank switching should work now
2014-12-21 adding dts folder and Makefile
2014-12-23 Adding more outputs to pario
2014-12-23 Working slightly better
2014-12-27 Working 16 channel PWM
2014-12-27 Cleanup, moving firmware stuff to it's own directory
2014-12-27 Updating gitignore
2014-12-27 Better memory management
2014-12-27 Cleaning up image slicer
2014-12-28 Adding c slicer
2014-12-28 Merging image slicer
2014-12-28 Removing dts
2014-12-29 Slicer uses argv input
2014-12-29 cleanup
2015-01-02 Added resistors (resolves #3), changed mosfet package (resolves #6), changed power input
2015-01-06 Adding blog folder
2015-01-06 .DS_Store files are bad and whoever invented them should feel bad
2015-01-06 Another sketch, LOI
2015-01-07 Blog, Start of Emu
2015-01-07 Moved _posts folder into blog folder
2015-01-10 Started adding A/B switches and more ports
2015-01-11 Work on routing A/B and mosfets
2015-01-12 Fixed blog/post layouts, adding gpmc draft
2015-01-12 Added a real footer
2015-01-12 More routing
2015-01-12 Adding fast DTS
2015-01-12 Adding anayltics
2015-01-12 Closed up the gap between sections
2015-01-12 I don't like big headers and I cannot lie
2015-01-13 Adding shitty 2D drawing
2015-01-15 Ripped up, starting over with new buffers
2015-01-16 Buffer all the things
2015-01-16 Adding gpmc device tree flags
2015-01-18 so much routing
2015-01-18 Done routing
2015-01-19 Rev B done
2015-01-19 Oops, adding resistors
2015-01-19 Updated year
2015-01-20 Finished new tft board
2015-01-20 Added solder mask to tft vias
2015-01-21 Updating bom info
2015-01-22 Removing old datasheets
2015-01-22 Adding backlight controller
2015-01-22 Ignoring _site
2015-01-31 Stub for virtual
2015-01-31 Basics
2015-01-31 Sort of working
2015-02-01 Add 8 pilars, a face mesh, ground, and a world.
2015-02-01 add the images
2015-02-03 cleaned up, backgroud texture, padding
2015-02-03 small fixes
2015-02-04 8 panels, ground, skybox, new controls
2015-02-05 Only update visible panels
2015-02-06 Updated MUX_S in dts
2015-02-06 Adding convert script
2015-02-06 Automatic scaledown based on FPS. Instructions.
2015-02-06 Grant Proposal
2015-02-06 Budget and Plan
2015-02-06 Reorg. Updated blog. Updated description.
2015-02-06 updated image case
2015-02-06 typo
2015-02-07 Added slicer support for dual screen banks
2015-02-07 Adding test slide generator
2015-02-07 Cleaning up the tft controller
2015-02-08 Updating totu.c to support banks
2015-02-09 Basic collision detection
2015-02-12 Refactor, fixed camera raycaster, needs map
2015-02-14 Updating backlight device tree overlay
2015-02-14 Updating BB-BONE-LOGIMAX to not step on cape
2015-02-14 Removing junk from dts
2015-02-14 Adding modified universal dts
2015-02-14 Needs some comments
2015-02-14 Needs some other stuff removed/added
2015-02-15 More dts changes
2015-02-15 Combined everything into one dts
2015-02-15 Cleaning up dts changes
2015-02-15 Chages to setup and tft.c
2015-02-15 Adding python test scripts
2015-02-16 Working backlights 1-7 (0 not working right)
2015-02-16 Support for banks
2015-02-16 please enjoy this mess
2015-02-16 Basic pixel mode working
2015-02-16 Cleaning up old pario stuff
2015-02-16 Adding the rest of the channels to totu.p and backlight.py
2015-02-17 Almost all 32 backlights working
2015-02-17 Cleaning up cape dts
2015-02-18 Cleaned up backlight stuff and commented
2015-02-19 Made the backlights work real nice
2015-02-19 Stripped the Makefile down to the bones
2015-02-19 Adding blog update and huge gif sorry
2015-02-20 Updated with new site design
2015-02-22 Separated MUX_S0 from MUX_S1 (fixes #30
2015-02-22 Replaced 5v rail with 3.3v rail (fixes #13)
2015-02-23 Adding firmware readme
2015-02-23 README formatting
2015-02-23 Updating README
2015-04-24 Added presliced mode, its got problems but is significantly slower due to network overhead. May be improved with direct ethernet connection. (WiFi->Eth was better than USB)
2015-04-24 Stencil
2015-04-24 Transmitter for TotU server
2015-04-24 fixed preslice, faster over ethernet
2015-04-24 Added documentation. Hopefully this will go in as me.
2015-04-24 Added bank selection
2015-04-24 Client in separate class. Added docs.
2015-05-11 Changed protocol to have two options bytes at beginning to set bank and presliced mode
2015-05-12 Support for 2 options bytes to set bank and presliced mode
2015-05-27 Frame
2015-05-27 no binaries
2015-05-29 Split initialization and slower dts for ishow testing
2015-05-29 Slower dts, faster than the ishow_hax branch
2015-05-30 Adding layout
2015-06-27 Server working

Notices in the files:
parts and their libraries:
SparkFun-Capacitors: Licensing: Creative Commons ShareAlike 4.0 International - https://creativecommons.org/licenses/by-sa/4.0
